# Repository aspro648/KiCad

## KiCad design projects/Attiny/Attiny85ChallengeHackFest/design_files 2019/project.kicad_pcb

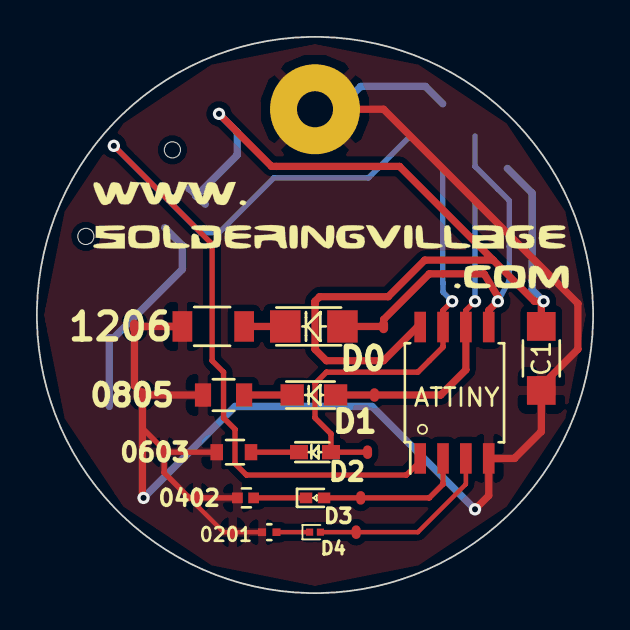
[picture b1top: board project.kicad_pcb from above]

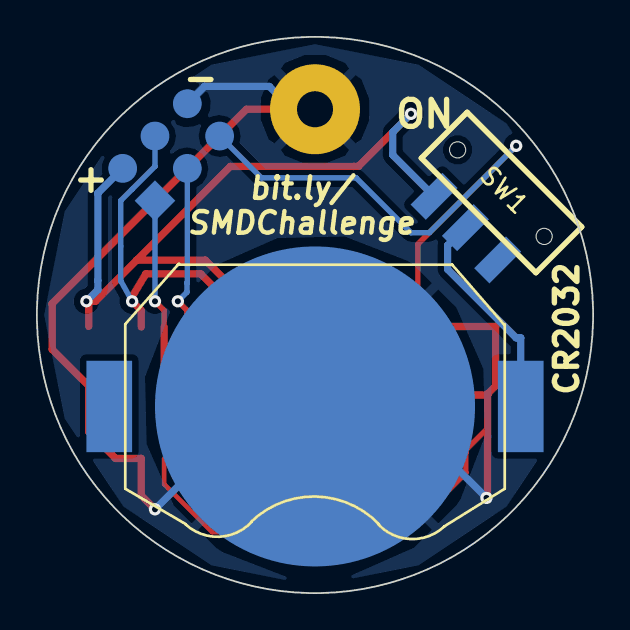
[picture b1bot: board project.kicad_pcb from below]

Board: 2 copper layers, 30.9 x 30.9 mm, 26 parts (3 on the bottom side), 14 nets.

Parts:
BT1: Battery; BATT_CR2032_SMD
C1: 0.1 uF; C_1206_HandSoldering
CON1: AVR-ISP-6
D0: LED; LED-1206
D1: LED; LED-0805
D2: LED; LED-0603
D3: LED; LED_0402
D4: LED; LED_0201
IC1: ATTINY; SOIJ-8_5.3x5.3mm_Pitch1.27mm
P0, P1, P2, P3, P4: CONN_01X01; testPad
P5: CONN_01X01; Pin_Header_Straight_1x01
PG0, PG1, PG2, PG3, PG4: CONN_01X01; testPad
R0: 330; R_1206
R1: 330; R_0805
R2: 330; R_0603
R3: 330; R_0402
R4: 330; R_0201
SW1: SW_SPDT; SPST_SMD

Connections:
+BATT: C1.2, CON1.2, IC1.8, SW1.3
GND: BT1.2, C1.1, CON1.6, IC1.4, P5.1, PG0.1, PG1.1, PG2.1, PG3.1, PG4.1, R0.2, R1.2, R2.2, R3.2, R4.2
unnamed: BT1.1, SW1.2
unnamed: CON1.1, D1.2, IC1.6, P1.1
unnamed: CON1.3, D2.2, IC1.7, P2.1
unnamed: CON1.4, D0.2, IC1.5, P0.1
unnamed: CON1.5, IC1.1
unnamed: D0.1, R0.1
unnamed: D1.1, R1.1
unnamed: D2.1, R2.1
unnamed: D3.1, R3.1
unnamed: D3.2, IC1.2, P3.1
unnamed: D4.1, R4.1
unnamed: D4.2, IC1.3, P4.1
